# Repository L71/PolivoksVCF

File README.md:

# PolivoksVCF
Polivoks style VCF eurorack module

8HP Eurorack module based on this schematic: http://m.bareille.free.fr/modular1/vcf_polivoks/vcf_polivoks.htm

See also https://l71.github.io/ for more info.

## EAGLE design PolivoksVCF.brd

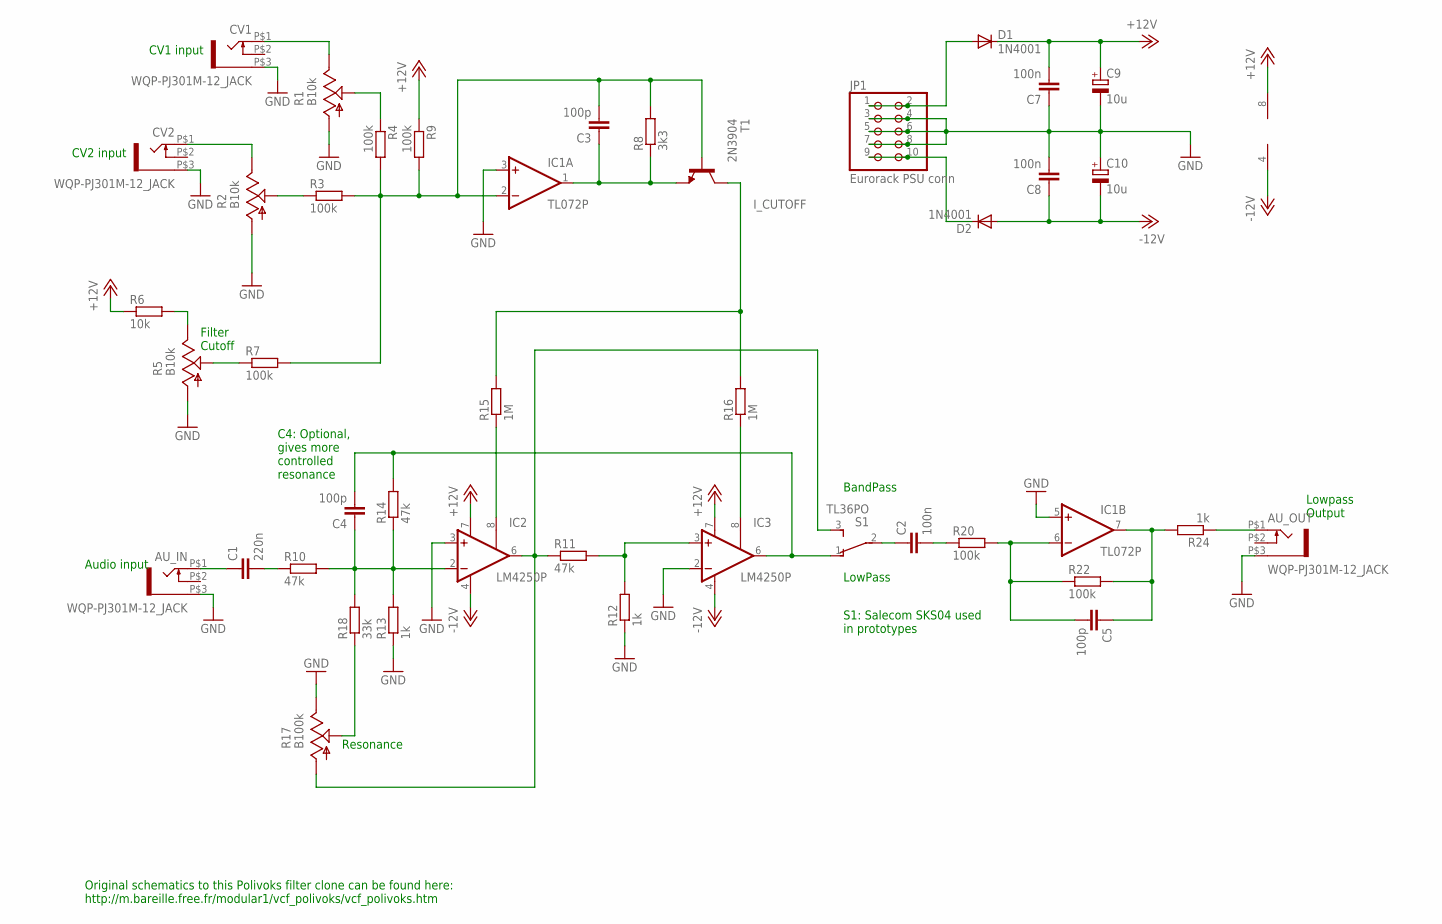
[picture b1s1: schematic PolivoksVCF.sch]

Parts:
AU_IN: WQP-PJ301M-12_JACK
AU_OUT: WQP-PJ301M-12_JACK
C1: 220n; C050-045X075
C2: 100n; C050-025X075
C3, C4, C5: 100p; C025-025X050
C7, C8: 100n; C025-025X050
C9, C10: 10u; E2,5-5
CV1, CV2: WQP-PJ301M-12_JACK
D1, D2: 1N4001; D-5
IC1: TL072P; DIL08
IC2, IC3: LM4250P; DIL08
JP1: Eurorack PSU conn; 2X05
R1, R2, R5: B10k; ALPS_POT_VERTICAL
R3, R4, R7, R9, R20, R22: 100k; 0207/2V
R6: 10k; 0207/2V
R8: 3k3; 0207/2V
R10, R11, R14: 47k; 0207/2V
R12, R13, R24: 1k; 0207/2V
R15, R16: 1M; 0207/2V
R17: B100k; ALPS_POT_VERTICAL
R18: 33k; 0207/2V
S1: TL36PO; TL3XPO
T1: 2N3904; TO92-EBC

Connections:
+12V: C7.2, C9.+, D1.C, IC1.8 (V+), IC2.7 (V+), IC3.7 (V+), R6.1, R9.1
-12V: C8.1, C10.-, D2.A, IC1.4 (V-), IC2.4 (V-), IC3.4 (V-)
BP_OUT: IC2.6 (OUT), R11.1, R17.P$3 (A), S1.3 (S)
GND: AU_IN.P$3 (1), AU_OUT.P$3 (1), C7.1, C8.2, C9.-, C10.+, CV1.P$3 (1), CV2.P$3 (1), IC1.3 (+IN), IC1.5 (+IN), IC2.3 (+IN), IC3.2 (-IN), JP1.3, JP1.4, JP1.5, JP1.6, JP1.7, JP1.8, R1.P$3 (A), R2.P$3 (A), R5.P$3 (A), R12.1, R13.1, R17.P$1 (E)
I_CUTOFF: R15.2, R16.2, T1.C
LP_OUT: C4.2, IC3.6 (OUT), R14.2, S1.1 (O)
unnamed: CV1.P$1 (2), R1.P$1 (E)
unnamed: CV2.P$1 (2), R2.P$1 (E)
unnamed: R5.P$1 (E), R6.2
unnamed: R5.P$2 (S), R7.1
unnamed: R2.P$2 (S), R3.1
unnamed: R1.P$2 (S), R4.1
unnamed: C3.2, IC1.2 (-IN), R3.2, R4.2, R7.2, R8.2, R9.2, T1.B
unnamed: C3.1, IC1.1 (OUT), R8.1, T1.E
unnamed: AU_IN.P$1 (2), C1.1
unnamed: C1.2, R10.1
unnamed: C4.1, IC2.2 (-IN), R10.2, R13.2, R14.1, R18.2
unnamed: IC3.3 (+IN), R11.2, R12.2
unnamed: IC2.8 (ISET), R15.1
unnamed: IC3.8 (ISET), R16.1
unnamed: C2.1, S1.2
unnamed: R17.P$2 (S), R18.1
unnamed: C5.1, IC1.7 (OUT), R22.2, R24.2
unnamed: C2.2, R20.1
unnamed: C5.2, IC1.6 (-IN), R20.2, R22.1
unnamed: AU_OUT.P$1 (2), R24.1
unnamed: D1.A, JP1.1, JP1.2
unnamed: D2.C, JP1.9, JP1.10

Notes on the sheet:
Resonance
Filter Cutoff
CV1 input
CV2 input
Audio input
Lowpass Output
LowPass
BandPass
C4: Optional, gives more controlled resonance
Original schematics to this Polivoks filter clone can be found here: http://m.bareille.free.fr/modular1/vcf_polivoks/vcf_polivoks.htm
S1: Salecom SKS04 used in prototypes

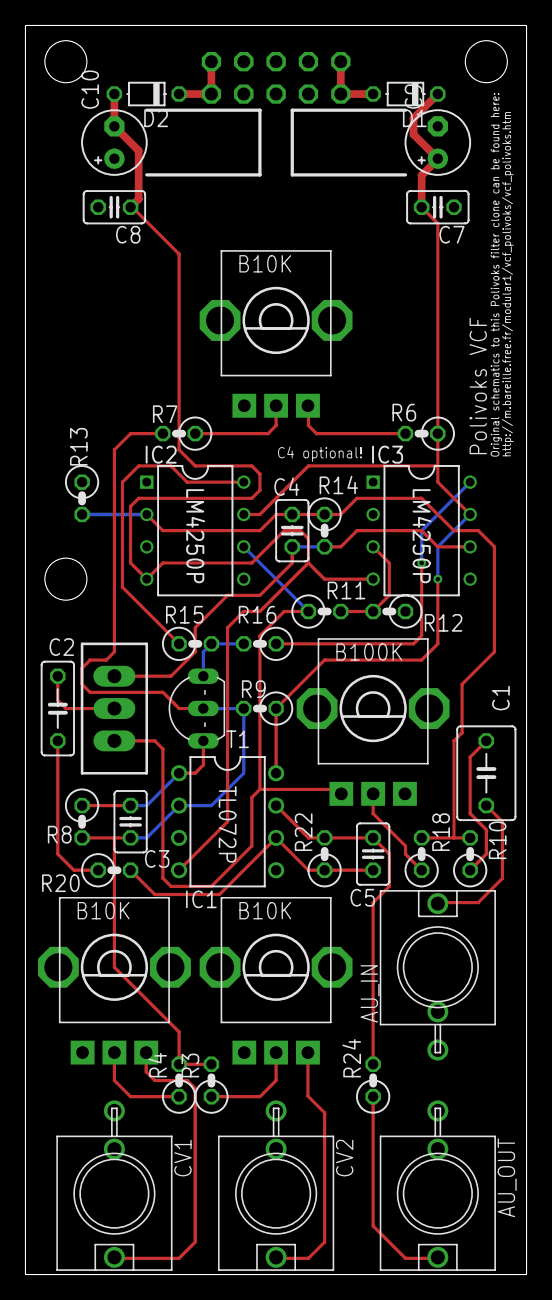
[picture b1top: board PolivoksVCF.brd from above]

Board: 2 copper layers, 39.4 x 98.1 mm, 42 parts (1 on the bottom side), 28 nets.

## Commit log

2017-09-05 initial add.
2017-09-05 Added original schematic file from The Internets.
2017-09-05 added link to original schematic
2017-09-07 Added board file & modified schematic, changed component footprints to vertical on all resistors.
2017-09-07 added polarity label to power connector
2017-09-07 Added labels to filter pcb. Added panel file.
2017-09-08 graphics fix.
2017-09-18 Added value to T1 so it shows up on schematic.
2017-09-18 Added note about type of S1.
2017-09-18 Added value labels to potentiometer footprints.
2017-09-20 Upload of ordered version, minus front (top) copper layer.
2017-10-22 Added readme.
2017-10-22 Fixed heading...
